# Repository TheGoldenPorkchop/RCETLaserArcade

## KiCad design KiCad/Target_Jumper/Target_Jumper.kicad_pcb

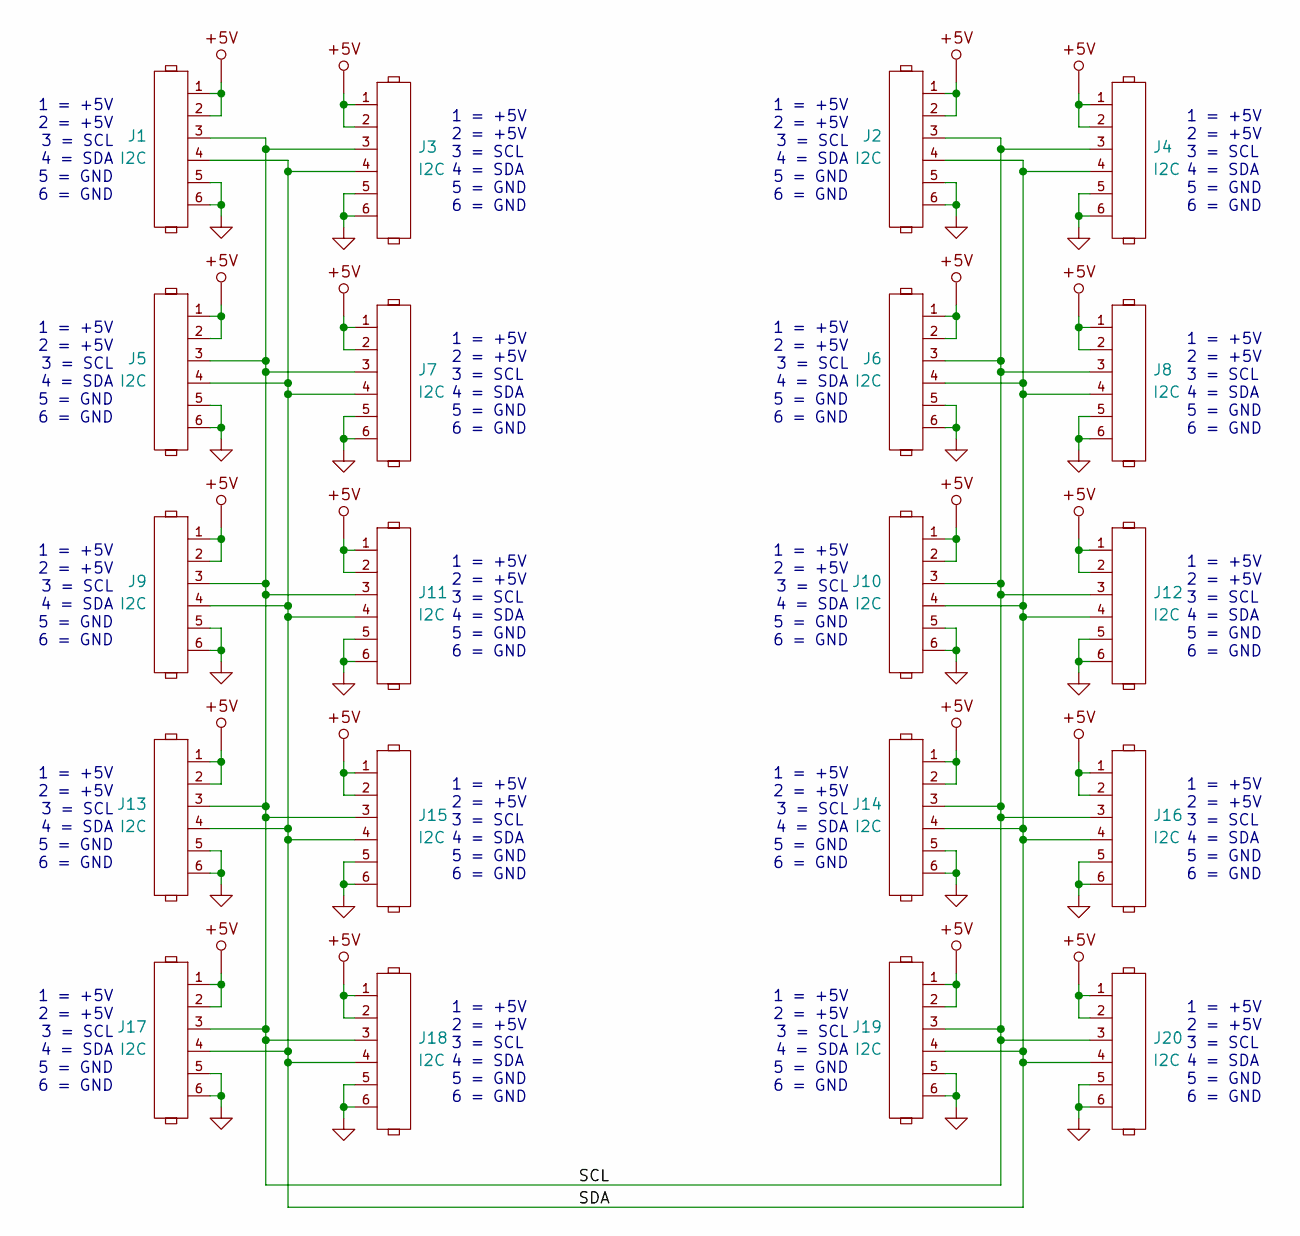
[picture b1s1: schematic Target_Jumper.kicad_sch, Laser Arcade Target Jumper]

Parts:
J1, J2, J3, J4, J5, J6, J7, J8, J9, J10, J11, J12, J13, J14, J15, J16, J17, J18, J19, J20: I2C; 1x6_100mil_Header

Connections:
+5V: J1.1, J1.2, J2.1, J2.2, J3.1, J3.2, J4.1, J4.2, J5.1, J5.2, J6.1, J6.2, J7.1, J7.2, J8.1, J8.2, J9.1, J9.2, J10.1, J10.2, J11.1, J11.2, J12.1, J12.2, J13.1, J13.2, J14.1, J14.2, J15.1, J15.2, J16.1, J16.2, J17.1, J17.2, J18.1, J18.2, J19.1, J19.2, J20.1, J20.2
/SCL: J1.3, J2.3, J3.3, J4.3, J5.3, J6.3, J7.3, J8.3, J9.3, J10.3, J11.3, J12.3, J13.3, J14.3, J15.3, J16.3, J17.3, J18.3, J19.3, J20.3
/SDA: J1.4, J2.4, J3.4, J4.4, J5.4, J6.4, J7.4, J8.4, J9.4, J10.4, J11.4, J12.4, J13.4, J14.4, J15.4, J16.4, J17.4, J18.4, J19.4, J20.4
GND: J1.5, J1.6, J2.5, J2.6, J3.5, J3.6, J4.5, J4.6, J5.5, J5.6, J6.5, J6.6, J7.5, J7.6, J8.5, J8.6, J9.5, J9.6, J10.5, J10.6, J11.5, J11.6, J12.5, J12.6, J13.5, J13.6, J14.5, J14.6, J15.5, J15.6, J16.5, J16.6, J17.5, J17.6, J18.5, J18.6, J19.5, J19.6, J20.5, J20.6

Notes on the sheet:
1 = +5V 2 = +5V 3 = SCL 4 = SDA 5 = GND 6 = GND

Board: 2 copper layers, 20 parts (0 on the bottom side), 4 nets, no tracks yet.

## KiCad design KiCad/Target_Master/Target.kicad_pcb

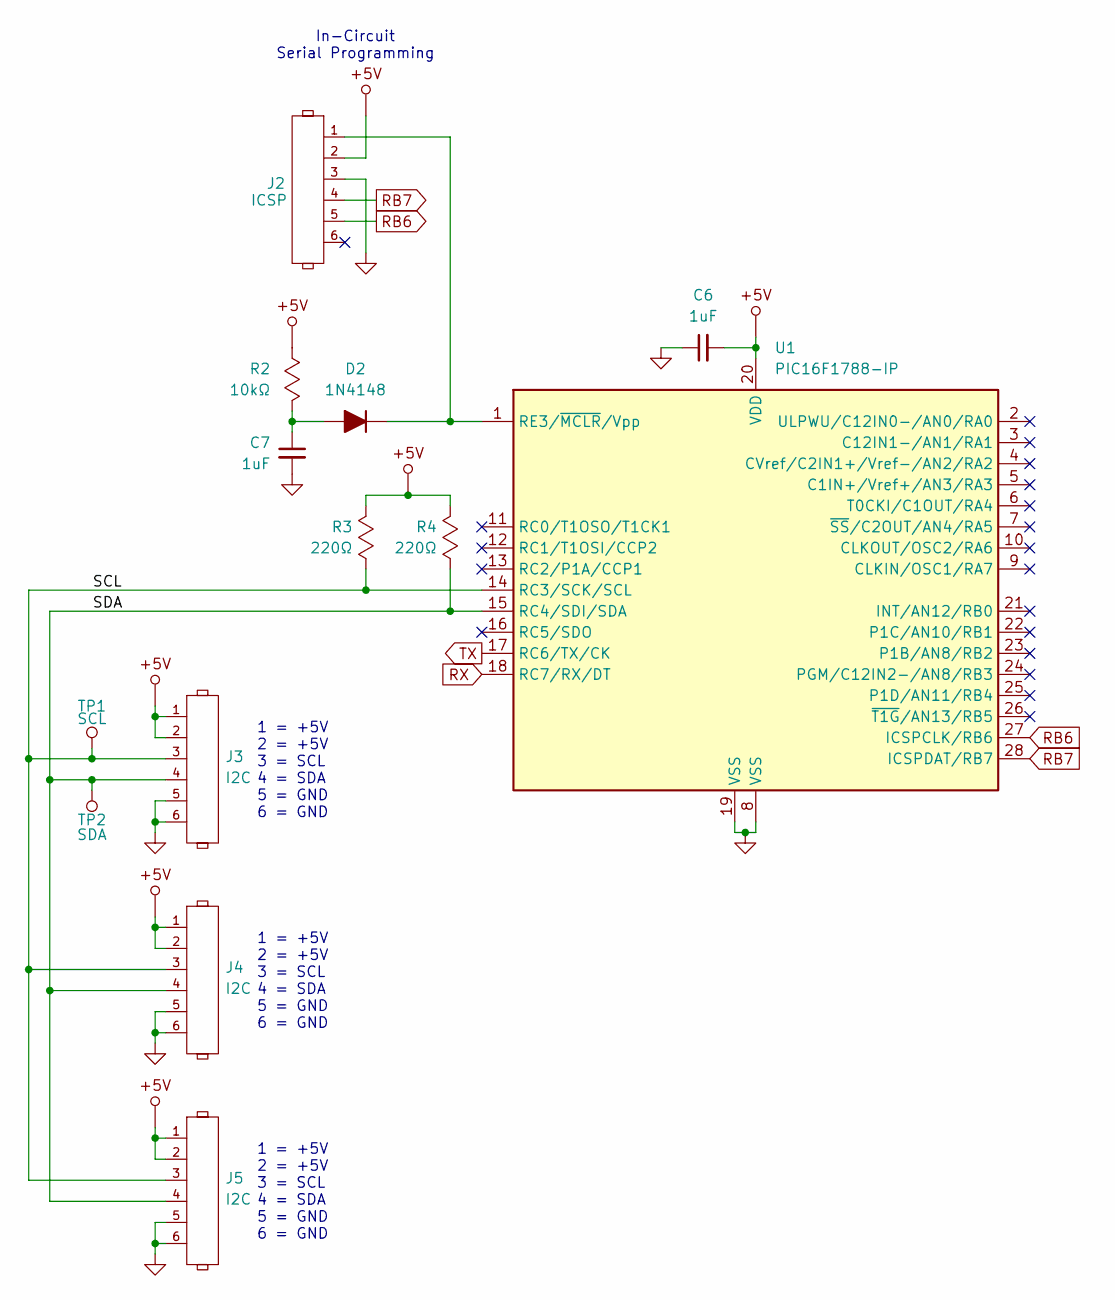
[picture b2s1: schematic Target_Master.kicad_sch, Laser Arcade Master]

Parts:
C6, C7: 1uF; C_0805_2012Metric_Pad1.18x1.45mm_HandSolder
D2: 1N4148; D_0805_2012Metric_Pad1.15x1.40mm_HandSolder
J2: ICSP; 1x6_100mil_Header
J3, J4, J5: I2C; 1x6_100mil_Header
R2: 10kΩ; R_0805_2012Metric_Pad1.20x1.40mm_HandSolder
R3, R4: 220Ω; R_0805_2012Metric_Pad1.20x1.40mm_HandSolder
TP1: SCL; 1x1_100mil_Header
TP2: SDA; 1x1_100mil_Header
U1: PIC16F1788-IP; SSOP-28

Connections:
+5V: C6.2, J2.2, J3.1, J3.2, J4.1, J4.2, J5.1, J5.2, R2.2, R3.1, R4.1, U1.20 (VDD); also elsewhere on the board
/Master/SCL: J3.3, J4.3, J5.3, R3.2, TP1.1, U1.14 (RC3/SCK/SCL)
/Master/SDA: J3.4, J4.4, J5.4, R4.2, TP2.1, U1.15 (RC4/SDI/SDA)
GND: C6.1, C7.2, J2.3, J3.5, J3.6, J4.5, J4.6, J5.5, J5.6, U1.8 (VSS), U1.19 (VSS); also elsewhere on the board
unnamed: C7.1, D2.2 (A), R2.1
unnamed: D2.1 (K), J2.1, U1.1 (RE3/~MCLR/Vpp)
RB6: J2.5, U1.27 (ICSPCLK/RB6)
RB7: J2.4, U1.28 (ICSPDAT/RB7)
RX: U1.18 (RC7/RX/DT); also elsewhere on the board
TX: U1.17 (RC6/TX/CK); also elsewhere on the board

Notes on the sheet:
In-Circuit Serial Programming
1 = +5V 2 = +5V 3 = SCL 4 = SDA 5 = GND 6 = GND

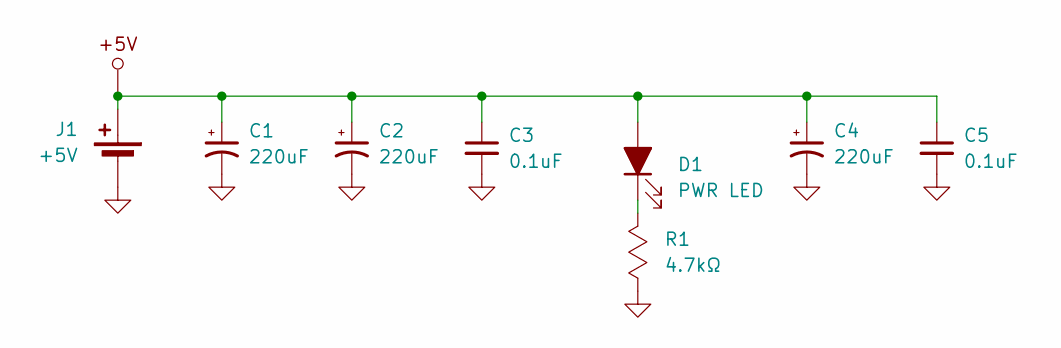
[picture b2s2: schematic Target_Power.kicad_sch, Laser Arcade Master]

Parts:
C1, C2, C4: 220uF; CP_Radial_D6.3mm_P2.50mm
C3, C5: 0.1uF; C_0805_2012Metric_Pad1.18x1.45mm_HandSolder
D1: PWR LED; LED_0805_2012Metric_Pad1.15x1.40mm_HandSolder
J1: +5V; AMASS_XT30PW-M_1x02_P2.50mm_Horizontal
R1: 4.7kΩ; R_0805_2012Metric_Pad1.20x1.40mm_HandSolder

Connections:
+5V: C1.1, C2.1, C3.1, C4.1, C5.1, D1.2 (A), J1.1 (+); also elsewhere on the board
GND: C1.2, C2.2, C3.2, C4.2, C5.2, J1.2 (-), R1.1; also elsewhere on the board
unnamed: D1.1 (K), R1.2

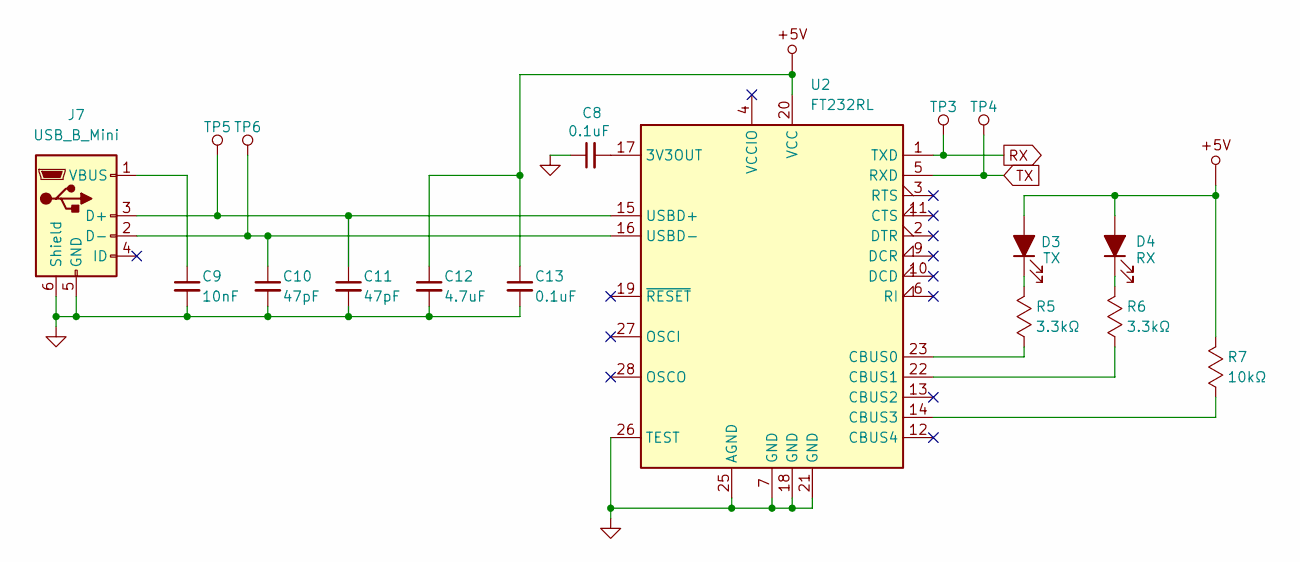
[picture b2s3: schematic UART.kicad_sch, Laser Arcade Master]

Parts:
C8, C13: 0.1uF; C_0805_2012Metric_Pad1.18x1.45mm_HandSolder
C9: 10nF; C_0805_2012Metric_Pad1.18x1.45mm_HandSolder
C10, C11: 47pF; C_0805_2012Metric_Pad1.18x1.45mm_HandSolder
C12: 4.7uF; C_0805_2012Metric_Pad1.18x1.45mm_HandSolder
D3: TX; LED_0805_2012Metric_Pad1.15x1.40mm_HandSolder
D4: RX; LED_0805_2012Metric_Pad1.15x1.40mm_HandSolder
J7: USB_B_Mini; USB_Micro-B_Amphenol
R5, R6: 3.3kΩ; R_0805_2012Metric_Pad1.20x1.40mm_HandSolder
R7: 10kΩ; R_0805_2012Metric_Pad1.20x1.40mm_HandSolder
TP3, TP4, TP5, TP6: 1x1_100mil_Header
U2: FT232RL; SSOP-28

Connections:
+5V: C12.1, C13.1, D3.2 (A), D4.2 (A), R7.2, U2.20 (VCC); also elsewhere on the board
GND: C8.1, C9.2, C10.2, C11.2, C12.2, C13.2, J7.5 (GND), J7.6 (Shield), U2.7 (GND), U2.18 (GND), U2.21 (GND), U2.25 (AGND), U2.26 (TEST); also elsewhere on the board
unnamed: D3.1 (K), R5.2
unnamed: D4.1 (K), R6.2
unnamed: C11.1, J7.3 (D+), TP5.1, U2.15 (USBD+)
unnamed: C10.1, J7.2 (D-), TP6.1, U2.16 (USBD-)
unnamed: C9.1, J7.1 (VBUS)
unnamed: C8.2, U2.17 (3V3OUT)
unnamed: R5.1, U2.23 (CBUS0)
unnamed: R6.1, U2.22 (CBUS1)
unnamed: R7.1, U2.14 (CBUS3)
RX: TP3.1, U2.1 (TXD); also elsewhere on the board
TX: TP4.1, U2.5 (RXD); also elsewhere on the board

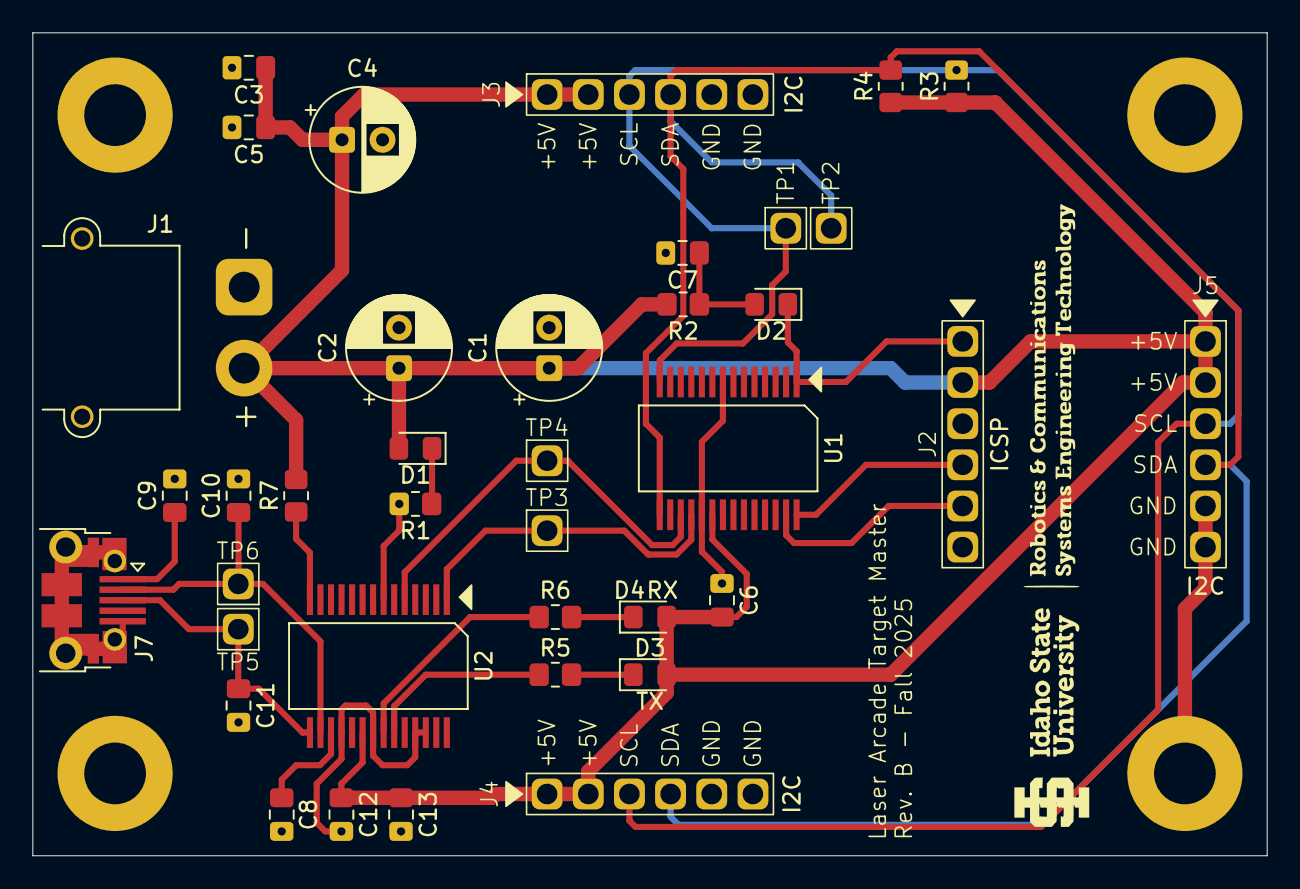
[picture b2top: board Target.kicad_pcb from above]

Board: 2 copper layers, 76.2 x 50.8 mm, 38 parts (0 on the bottom side), 20 nets.

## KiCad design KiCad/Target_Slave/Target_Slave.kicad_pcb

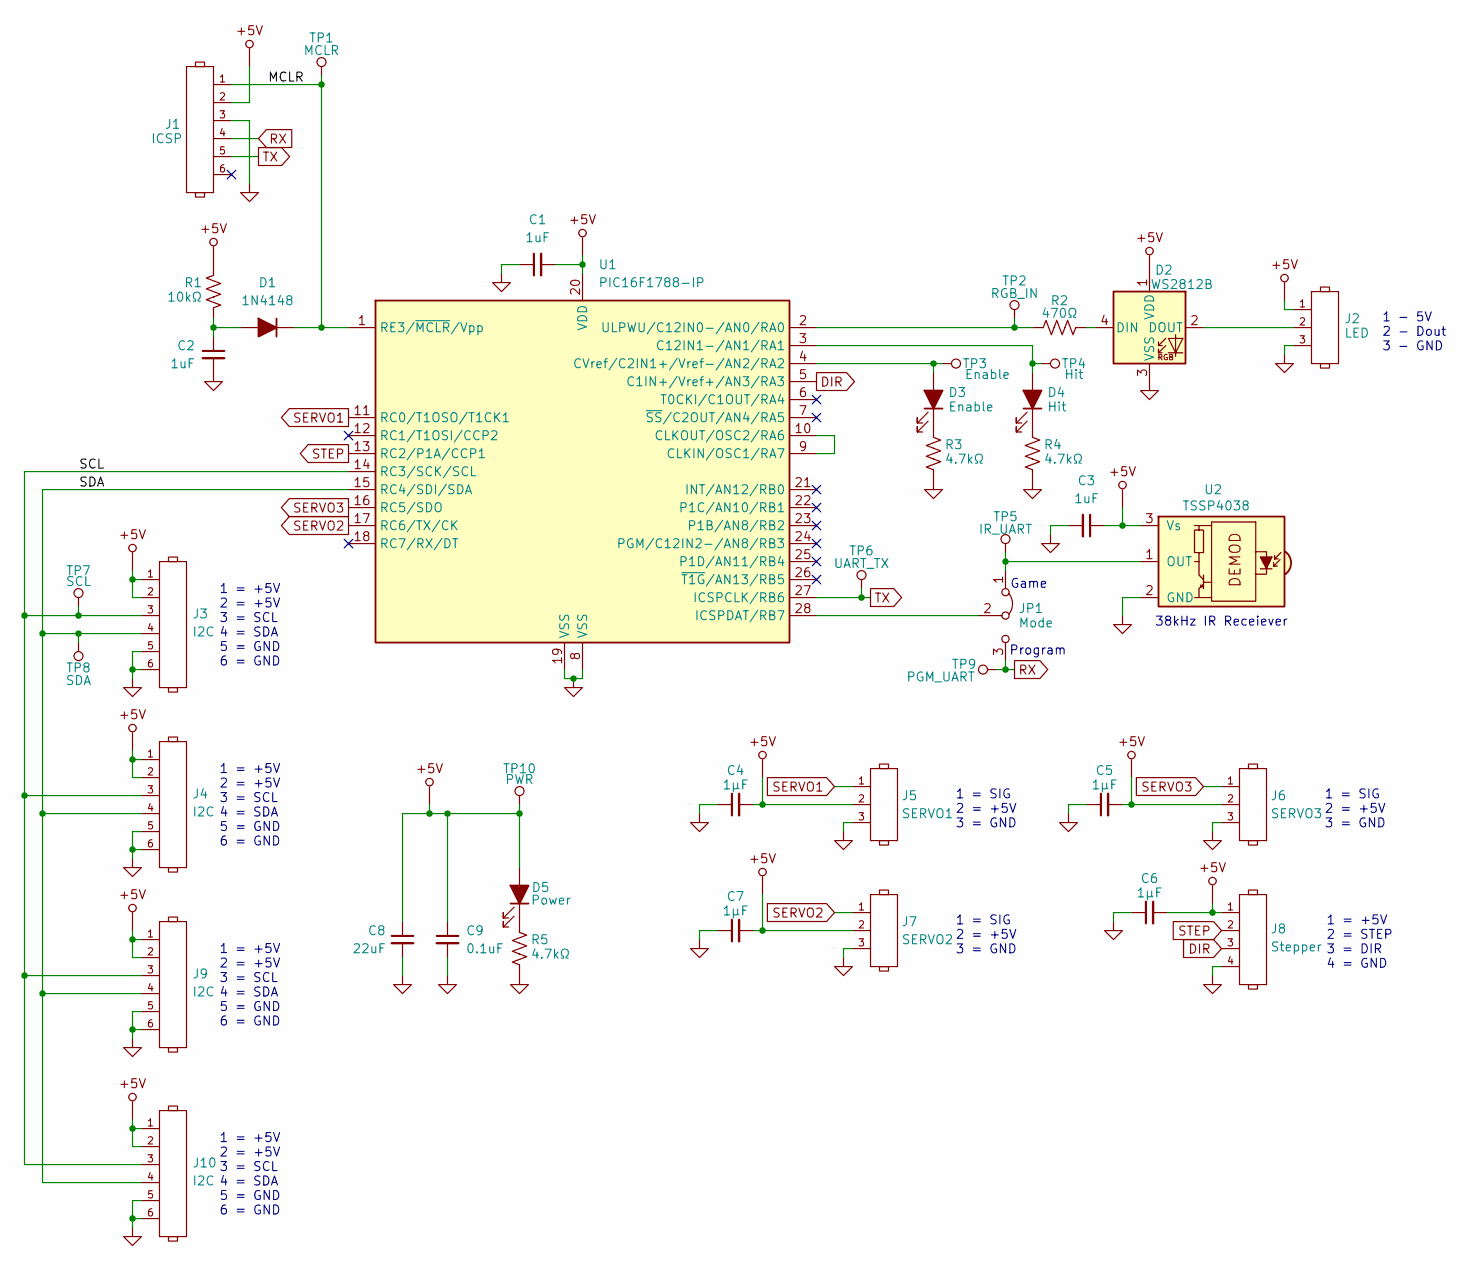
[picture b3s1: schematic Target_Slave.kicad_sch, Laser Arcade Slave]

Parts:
C1, C2, C3: 1uF; C_0805_2012Metric_Pad1.18x1.45mm_HandSolder
C4, C5, C6, C7: 1µF; C_0805_2012Metric_Pad1.18x1.45mm_HandSolder
C8: 22uF; C_0805_2012Metric_Pad1.18x1.45mm_HandSolder
C9: 0.1uF; C_0805_2012Metric_Pad1.18x1.45mm_HandSolder
D1: 1N4148; D_0805_2012Metric_Pad1.15x1.40mm_HandSolder
D2: WS2812B; LED_WS2812B_PLCC4_5.0x5.0mm_P3.2mm
D3: Enable; LED_0805_2012Metric_Pad1.15x1.40mm_HandSolder
D4: Hit; LED_0805_2012Metric_Pad1.15x1.40mm_HandSolder
D5: Power; LED_0805_2012Metric_Pad1.15x1.40mm_HandSolder
J1: ICSP; 1x6_100mil_Header
J2: LED; 1x3_100mil_Header_Locking
J3, J4, J9, J10: I2C; 1x6_100mil_Header
J5: SERVO1; 1x3_100mil_Header
J6: SERVO3; 1x3_100mil_Header
J7: SERVO2; 1x3_100mil_Header
J8: Stepper; 1x4_100mil_Header
JP1: Mode; 1x3_100mil_Header
R1: 10kΩ; R_0805_2012Metric_Pad1.20x1.40mm_HandSolder
R2: 470Ω; R_0805_2012Metric_Pad1.20x1.40mm_HandSolder
R3, R4, R5: 4.7kΩ; R_0805_2012Metric_Pad1.20x1.40mm_HandSolder
TP1: MCLR; 1x1_100mil_Header
TP2: RGB_IN; 1x1_100mil_Header
TP3: Enable; 1x1_100mil_Header
TP4: Hit; 1x1_100mil_Header
TP5: IR_UART; 1x1_100mil_Header
TP6: UART_TX; 1x1_100mil_Header
TP7: SCL; 1x1_100mil_Header
TP8: SDA; 1x1_100mil_Header
TP9: PGM_UART; 1x1_100mil_Header
TP10: PWR; 1x1_100mil_Header
U1: PIC16F1788-IP; SSOP-28
U2: TSSP4038; IR Receiver

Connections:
+5V: C1.2, C3.1, C4.2, C5.2, C6.2, C7.2, C8.1, C9.1, D2.1 (VDD), D5.2 (A), J1.2, J2.1, J3.1, J3.2, J4.1, J4.2, J5.2, J6.2, J7.2, J8.1, J9.1, J9.2, J10.1, J10.2, R1.1, TP10.1, U1.20 (VDD), U2.3 (Vs)
/MCLR: D1.1 (K), J1.1, TP1.1, U1.1 (RE3/~MCLR/Vpp)
/SCL: J3.3, J4.3, J9.3, J10.3, TP7.1, U1.14 (RC3/SCK/SCL)
/SDA: J3.4, J4.4, J9.4, J10.4, TP8.1, U1.15 (RC4/SDI/SDA)
DIR: J8.3, U1.5 (C1IN+/Vref+/AN3/RA3)
GND: C1.1, C2.2, C3.2, C4.1, C5.1, C6.1, C7.1, C8.2, C9.2, D2.3 (VSS), J1.3, J2.3, J3.5, J3.6, J4.5, J4.6, J5.3, J6.3, J7.3, J8.4, J9.5, J9.6, J10.5, J10.6, R3.2, R4.2, R5.2, U1.8 (VSS), U1.19 (VSS), U2.2 (GND)
unnamed: C2.1, D1.2 (A), R1.2
unnamed: D2.4 (DIN), R2.2
unnamed: D2.2 (DOUT), J2.2
unnamed: D3.2 (A), TP3.1, U1.4 (CVref/C2IN1+/Vref-/AN2/RA2)
unnamed: D3.1 (K), R3.1
unnamed: D4.2 (A), TP4.1, U1.3 (C12IN1-/AN1/RA1)
unnamed: D4.1 (K), R4.1
unnamed: D5.1 (K), R5.1
unnamed: JP1.1 (A), TP5.1, U2.1 (OUT)
unnamed: JP1.2 (C), U1.28 (ICSPDAT/RB7)
unnamed: U1.9 (CLKIN/OSC1/RA7), U1.10 (CLKOUT/OSC2/RA6)
unnamed: R2.1, TP2.1, U1.2 (ULPWU/C12IN0-/AN0/RA0)
RX: J1.4, JP1.3 (B), TP9.1
SERVO1: J5.1, U1.11 (RC0/T1OSO/T1CK1)
SERVO2: J7.1, U1.17 (RC6/TX/CK)
SERVO3: J6.1, U1.16 (RC5/SDO)
STEP: J8.2, U1.13 (RC2/P1A/CCP1)
TX: J1.5, TP6.1, U1.27 (ICSPCLK/RB6)

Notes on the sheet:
1 = +5V 2 = STEP 3 = DIR 4 = GND
1 = +5V 2 = +5V 3 = SCL 4 = SDA 5 = GND 6 = GND
Program
1 = SIG 2 = +5V 3 = GND
1 - 5V 2 - Dout 3 - GND
Game
38kHz IR Receiever

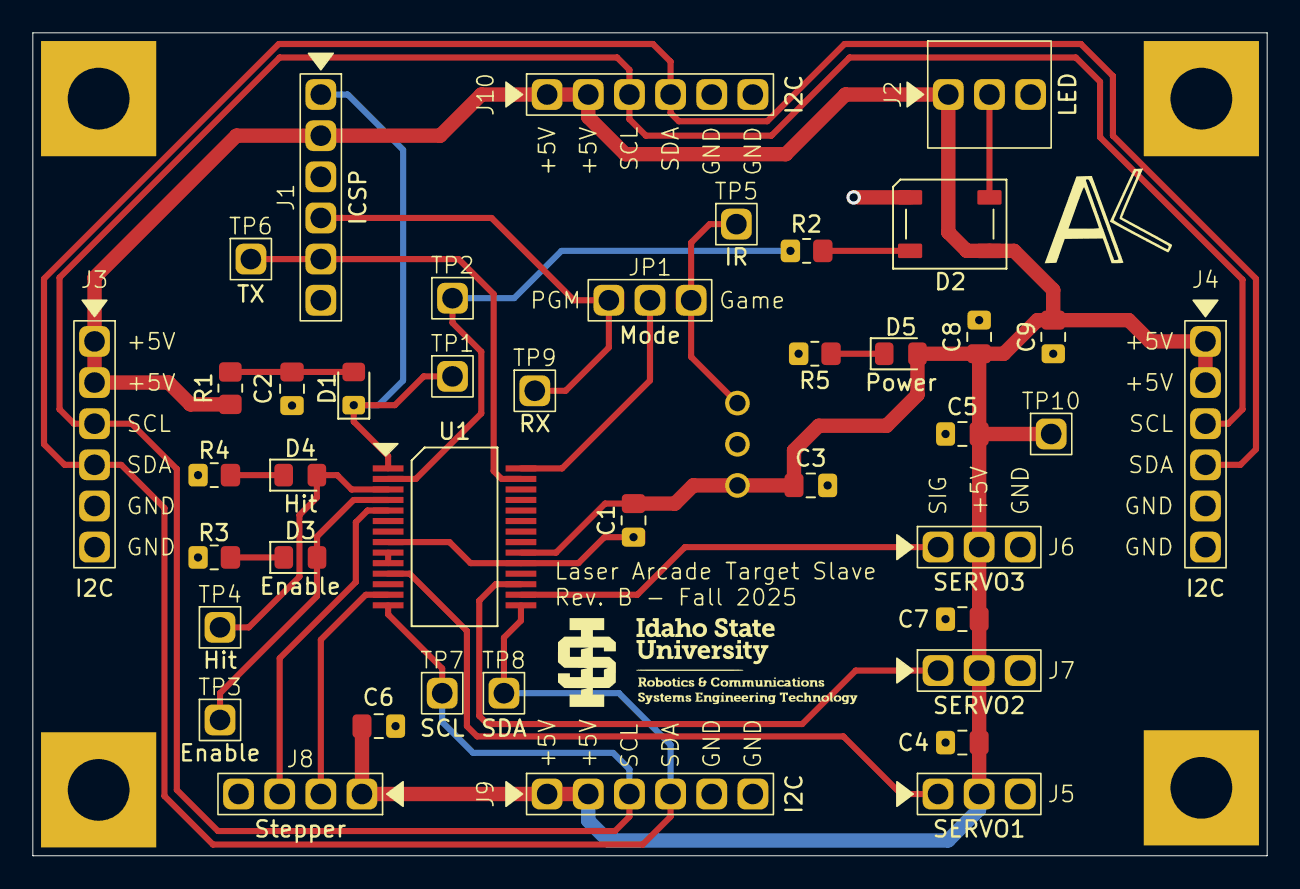
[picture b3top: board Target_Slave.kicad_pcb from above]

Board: 2 copper layers, 76.2 x 50.8 mm, 42 parts (1 on the bottom side), 24 nets.

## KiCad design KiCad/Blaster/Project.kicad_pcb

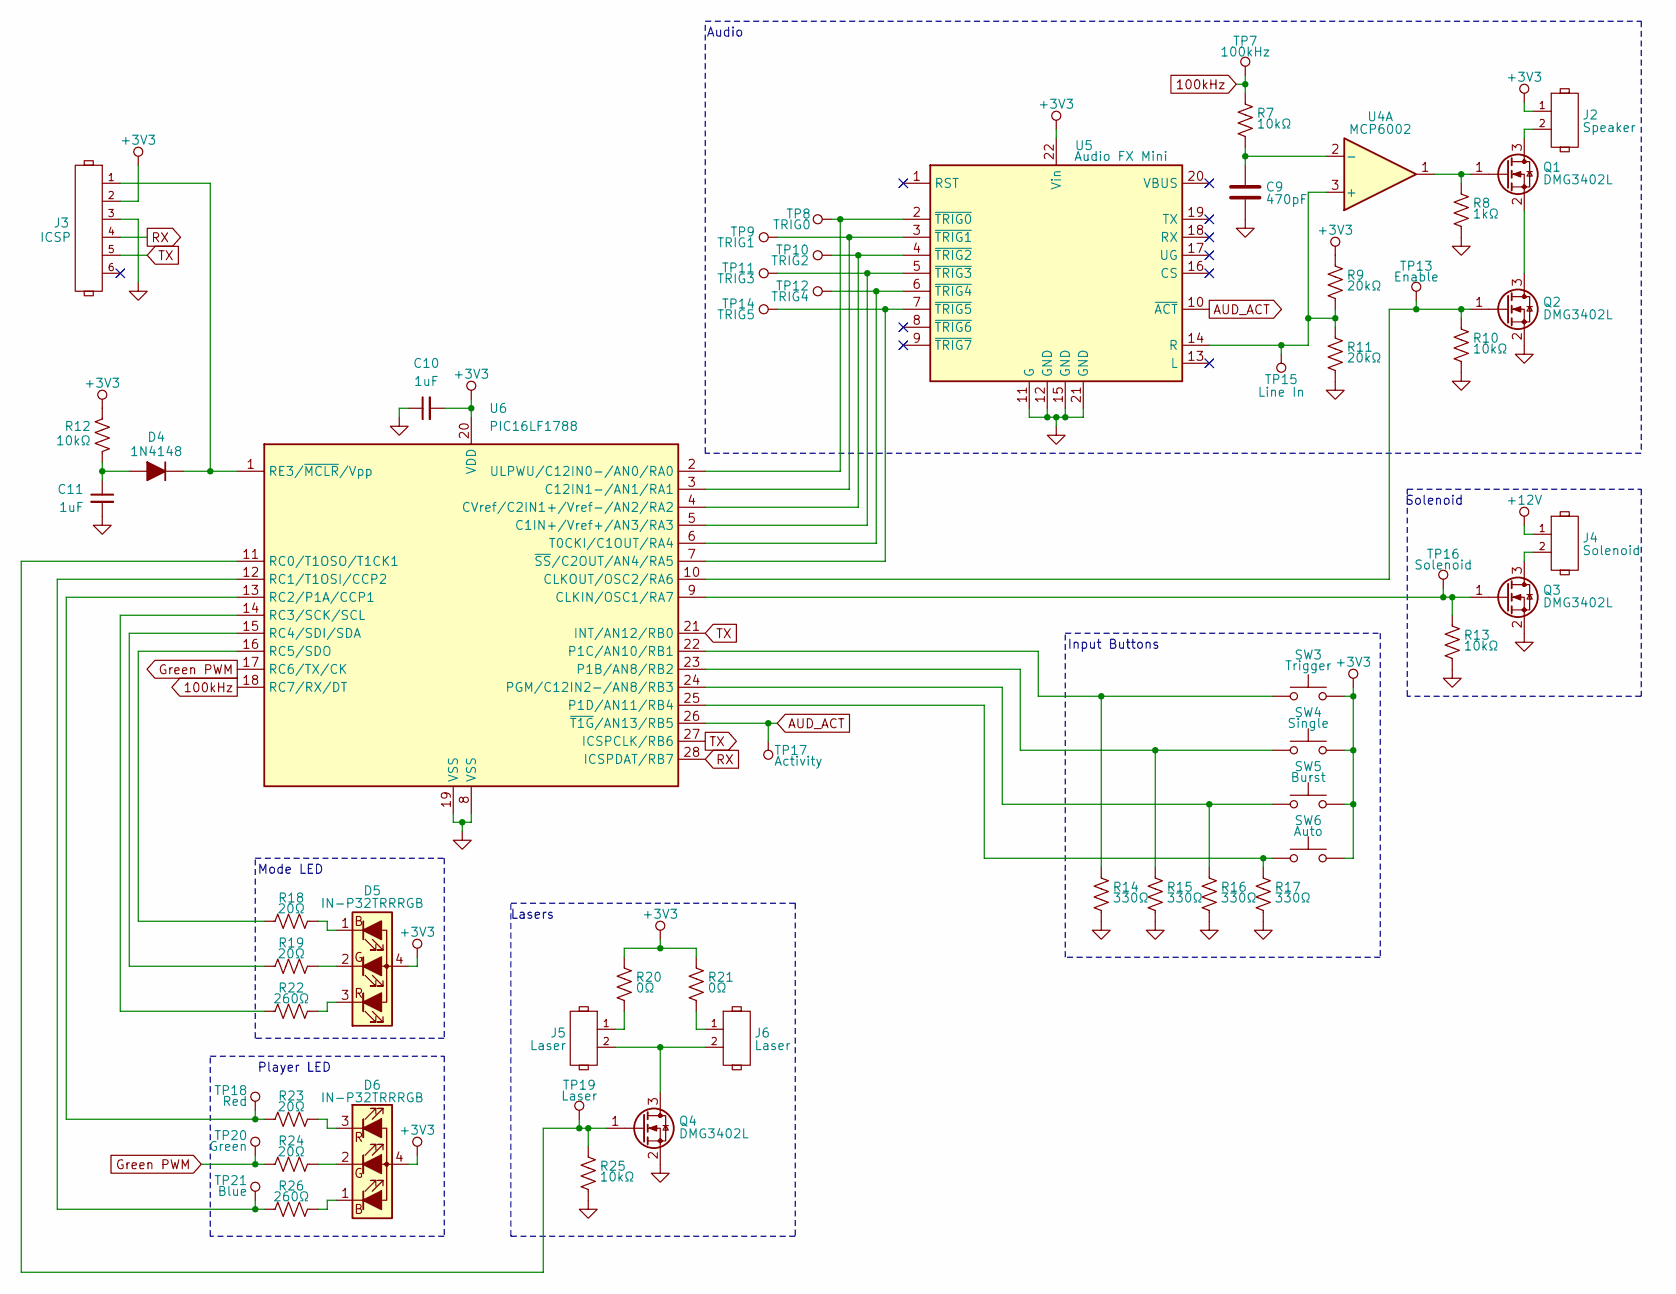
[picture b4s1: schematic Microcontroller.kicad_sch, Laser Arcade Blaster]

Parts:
C9: 470pF; C_0805_2012Metric_Pad1.18x1.45mm_HandSolder
C10, C11: 1uF; C_0805_2012Metric_Pad1.18x1.45mm_HandSolder
D4: 1N4148; D_0805_2012Metric_Pad1.15x1.40mm_HandSolder
D5, D6: IN-P32TRRRGB
J2: Speaker; 1x2_100mil_Header_Locking
J3: ICSP; 1x6_100mil_Header
J4: Solenoid; 1x2_100mil_Header_Locking
J5, J6: Laser; 1x2_100mil_Header_Locking
Q1, Q2, Q3, Q4: DMG3402L; SOT-23
R7, R10, R12, R13, R25: 10kΩ; R_0805_2012Metric_Pad1.20x1.40mm_HandSolder
R8: 1kΩ; R_0805_2012Metric_Pad1.20x1.40mm_HandSolder
R9, R11: 20kΩ; R_0805_2012Metric_Pad1.20x1.40mm_HandSolder
R14, R15, R16, R17: 330Ω; R_0805_2012Metric_Pad1.20x1.40mm_HandSolder
R18, R19, R23, R24: 20Ω; R_0805_2012Metric_Pad1.20x1.40mm_HandSolder
R20, R21: 0Ω; R_0805_2012Metric_Pad1.20x1.40mm_HandSolder
R22, R26: 260Ω; R_0805_2012Metric_Pad1.20x1.40mm_HandSolder
SW3: Trigger; SW_Tactile_SPST_Angled_PTS645Vx31-2LFS
SW4: Single; SW_PUSH_6mm_H5mm
SW5: Burst; SW_PUSH_6mm_H5mm
SW6: Auto; SW_PUSH_6mm_H5mm
TP7: 100kHz; 1x1_100mil_Header
TP8: TRIG0; 1x1_100mil_Header
TP9: TRIG1; 1x1_100mil_Header
TP10: TRIG2; 1x1_100mil_Header
TP11: TRIG3; 1x1_100mil_Header
TP12: TRIG4; 1x1_100mil_Header
TP13: Enable; 1x1_100mil_Header
TP14: TRIG5; 1x1_100mil_Header
TP15: Line In; 1x1_100mil_Header
TP16: Solenoid; 1x1_100mil_Header
TP17: Activity; 1x1_100mil_Header
TP18: Red; 1x1_100mil_Header
TP19: Laser; 1x1_100mil_Header
TP20: Green; 1x1_100mil_Header
TP21: Blue; 1x1_100mil_Header
U4: MCP6002; SOIC-8_3.9x4.9mm_P1.27mm
U5: Audio FX Mini; Adafruit_AudioFXMini
U6: PIC16LF1788; SSOP-28

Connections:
100kHz: R7.1, TP7.1, U6.18 (RC7/RX/DT)
+3V3: C10.2, D5.4 (A), D6.4 (A), J2.1, J3.2, R9.1, R12.1, R20.1, R21.1, SW3.2, SW4.2, SW5.2, SW6.2, U5.22 (Vin), U6.20 (VDD); also elsewhere on the board
+12V: J4.1; also elsewhere on the board
AUD_ACT: TP17.1, U5.10 (~ACT), U6.26 (~T1G/AN13/RB5)
GND: C9.2, C10.1, C11.2, J3.3, Q2.2 (S), Q3.2 (S), Q4.2 (S), R8.2, R10.2, R11.2, R13.2, R14.2, R15.2, R16.2, R17.2, R25.2, U5.11 (G), U5.12 (GND), U5.15 (GND), U5.21 (GND), U6.8 (VSS), U6.19 (VSS); also elsewhere on the board
Green PWM: R24.1, TP20.1, U6.17 (RC6/TX/CK)
unnamed: C11.1, D4.2 (A), R12.2
unnamed: D4.1 (K), J3.1, U6.1 (RE3/~MCLR/Vpp)
unnamed: D5.1 (BK), R18.2
unnamed: D5.2 (GK), R19.2
unnamed: D5.3 (RK), R22.2
unnamed: D6.1 (BK), R26.2
unnamed: D6.2 (GK), R24.2
unnamed: D6.3 (RK), R23.2
unnamed: J5.1, R20.2
unnamed: J6.1, R21.2
unnamed: J2.2, Q1.3 (D)
unnamed: Q1.1 (G), R8.1, U4.1
unnamed: Q1.2 (S), Q2.3 (D)
unnamed: Q2.1 (G), R10.1, TP13.1, U6.10 (CLKOUT/OSC2/RA6)
unnamed: J4.2, Q3.3 (D)
unnamed: Q3.1 (G), R13.1, TP16.1, U6.9 (CLKIN/OSC1/RA7)
unnamed: J5.2, J6.2, Q4.3 (D)
unnamed: Q4.1 (G), R25.1, TP19.1, U6.11 (RC0/T1OSO/T1CK1)
unnamed: R9.2, R11.1, TP15.1, U4.3 (+), U5.14 (R)
unnamed: C9.1, R7.2, U4.2 (-)
unnamed: TP8.1, U5.2 (~TRIG0), U6.2 (ULPWU/C12IN0-/AN0/RA0)
unnamed: TP9.1, U5.3 (~TRIG1), U6.3 (C12IN1-/AN1/RA1)
unnamed: TP10.1, U5.4 (~TRIG2), U6.4 (CVref/C2IN1+/Vref-/AN2/RA2)
unnamed: TP11.1, U5.5 (~TRIG3), U6.5 (C1IN+/Vref+/AN3/RA3)
unnamed: TP12.1, U5.6 (~TRIG4), U6.6 (T0CKI/C1OUT/RA4)
unnamed: TP14.1, U5.7 (~TRIG5), U6.7 (~SS/C2OUT/AN4/RA5)
unnamed: R15.1, SW4.1, U6.23 (P1B/AN8/RB2)
unnamed: R14.1, SW3.1, U6.22 (P1C/AN10/RB1)
unnamed: R17.1, SW6.1, U6.25 (P1D/AN11/RB4)
unnamed: R16.1, SW5.1, U6.24 (PGM/C12IN2-/AN8/RB3)
unnamed: R26.1, TP21.1, U6.12 (RC1/T1OSI/CCP2)
unnamed: R23.1, TP18.1, U6.13 (RC2/P1A/CCP1)
unnamed: R22.1, U6.14 (RC3/SCK/SCL)
unnamed: R19.1, U6.15 (RC4/SDI/SDA)
unnamed: R18.1, U6.16 (RC5/SDO)
RX: J3.4, U6.28 (ICSPDAT/RB7); also elsewhere on the board
TX: J3.5, U6.21 (INT/AN12/RB0), U6.27 (ICSPCLK/RB6); also elsewhere on the board

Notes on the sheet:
Solenoid
Mode LED
Player LED
Lasers
Input Buttons
Audio

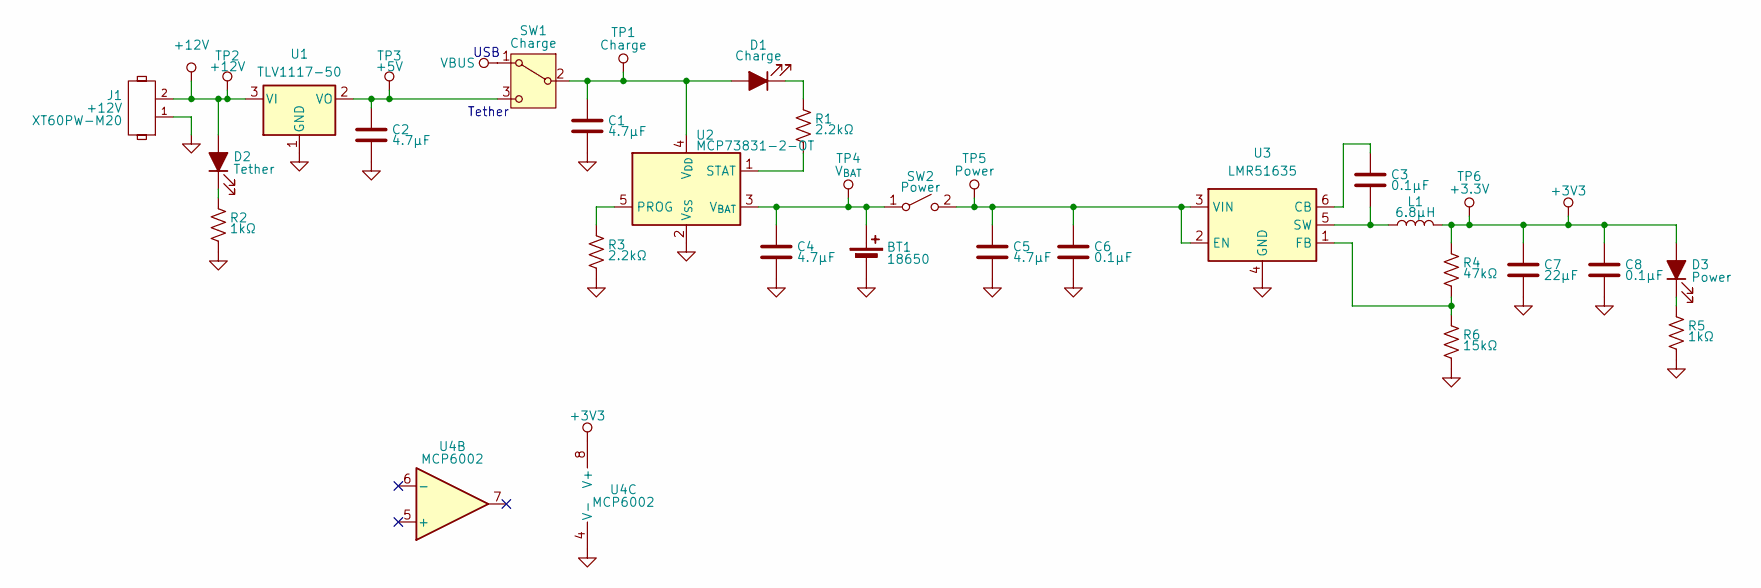
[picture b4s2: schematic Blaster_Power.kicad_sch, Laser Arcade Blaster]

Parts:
BT1: 18650; BatteryHolder_Keystone_1042_1x18650
C1, C2, C4, C5: 4.7µF; C_0805_2012Metric_Pad1.18x1.45mm_HandSolder
C3, C6, C8: 0.1µF; C_0805_2012Metric_Pad1.18x1.45mm_HandSolder
C7: 22µF; C_0805_2012Metric_Pad1.18x1.45mm_HandSolder
D1: Charge; LED_0805_2012Metric_Pad1.15x1.40mm_HandSolder
D2: Tether; LED_0805_2012Metric_Pad1.15x1.40mm_HandSolder
D3: Power; LED_0805_2012Metric_Pad1.15x1.40mm_HandSolder
J1: +12V; AMASS_XT60PW-M_1x02_P7.20mm_Horizontal
L1: 6.8µH; LA Blaster Power Inductor
R1, R3: 2.2kΩ; R_0805_2012Metric_Pad1.20x1.40mm_HandSolder
R2, R5: 1kΩ; R_0805_2012Metric_Pad1.20x1.40mm_HandSolder
R4: 47kΩ; R_0805_2012Metric_Pad1.20x1.40mm_HandSolder
R6: 15kΩ; R_0805_2012Metric_Pad1.20x1.40mm_HandSolder
SW1: Charge; T80-T
SW2: Power; LA Blaster Power Switch
TP1: Charge; 1x1_100mil_Header
TP2: +12V; 1x1_100mil_Header
TP3: +5V; 1x1_100mil_Header
TP4: V_{BAT}; 1x1_100mil_Header
TP5: Power; 1x1_100mil_Header
TP6: +3.3V; 1x1_100mil_Header
U1: TLV1117-50; SOT-223-3_TabPin2
U2: MCP73831-2-OT; SOT-23-5_HandSoldering
U3: LMR51635; SOT-23-6_Handsoldering
U4: MCP6002; SOIC-8_3.9x4.9mm_P1.27mm

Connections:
+3V3: C7.1, C8.1, D3.2 (A), L1.2, R4.1, TP6.1, U4.8 (V+); also elsewhere on the board
+12V: D2.2 (A), J1.2, TP2.1, U1.3 (VI); also elsewhere on the board
GND: BT1.2 (-), C1.2, C2.2, C4.2, C5.2, C6.2, C7.2, C8.2, J1.1, R2.2, R3.2, R5.2, R6.2, U1.1 (GND), U2.2 (V_{SS}), U3.4 (GND), U4.4 (V-); also elsewhere on the board
unnamed: BT1.1 (+), C4.1, SW2.1 (A), TP4.1, U2.3 (V_{BAT})
unnamed: C1.1, D1.2 (A), SW1.2 (B), TP1.1, U2.4 (V_{DD})
unnamed: D1.1 (K), R1.1
unnamed: D2.1 (K), R2.1
unnamed: D3.1 (K), R5.1
unnamed: C2.1, SW1.3 (C), TP3.1, U1.2 (VO)
unnamed: C5.1, C6.1, SW2.2 (B), TP5.1, U3.2 (EN), U3.3 (VIN)
unnamed: R3.1, U2.5 (PROG)
unnamed: R1.2, U2.1 (STAT)
unnamed: C3.1, U3.6 (CB)
unnamed: R4.2, R6.1, U3.1 (FB)
unnamed: C3.2, L1.1, U3.5 (SW)
VBUS: SW1.1 (A); also elsewhere on the board

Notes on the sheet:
Tether
USB

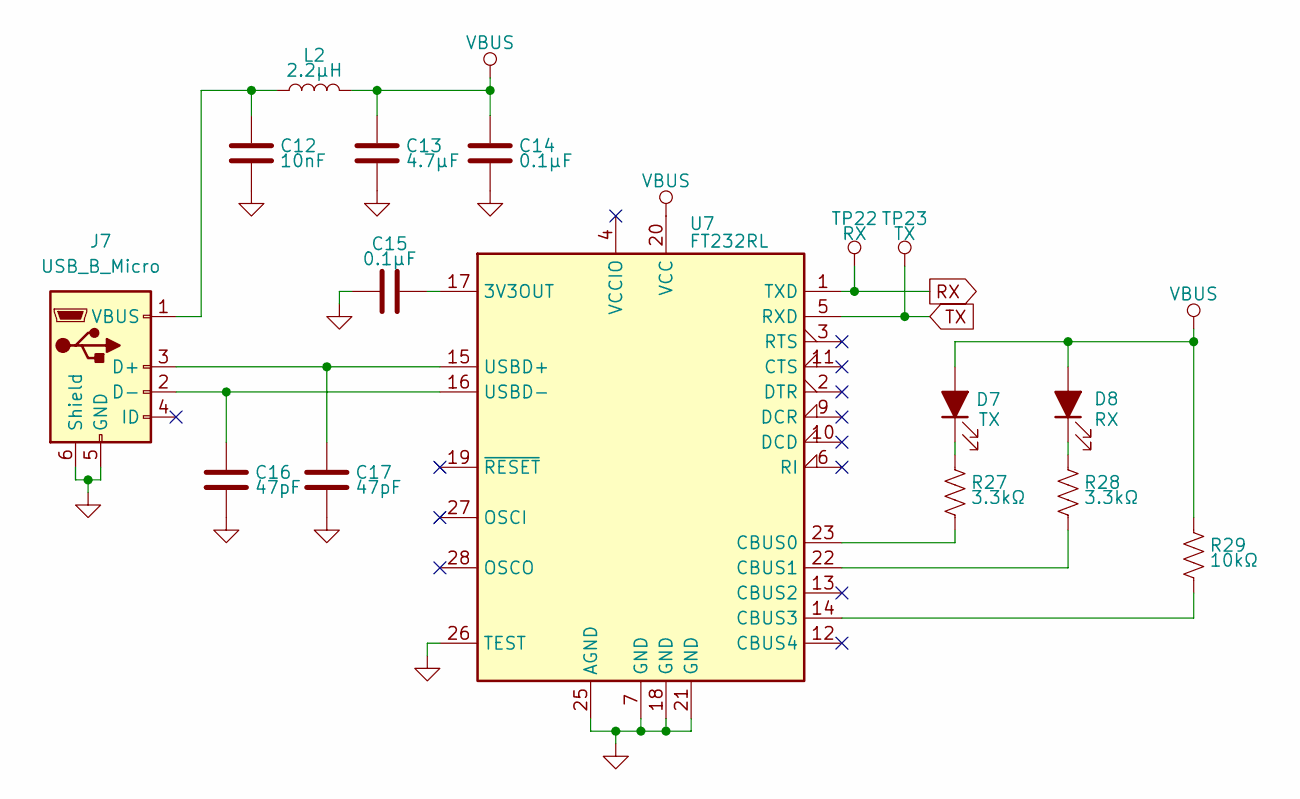
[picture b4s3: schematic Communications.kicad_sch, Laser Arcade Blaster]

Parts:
C12: 10nF; C_0805_2012Metric_Pad1.18x1.45mm_HandSolder
C13: 4.7µF; C_0805_2012Metric_Pad1.18x1.45mm_HandSolder
C14, C15: 0.1µF; C_0805_2012Metric_Pad1.18x1.45mm_HandSolder
C16, C17: 47pF; C_0805_2012Metric_Pad1.18x1.45mm_HandSolder
D7: TX; LED_0805_2012Metric_Pad1.15x1.40mm_HandSolder
D8: RX; LED_0805_2012Metric_Pad1.15x1.40mm_HandSolder
J7: USB_B_Micro; USB_Micro-B_Amphenol
L2: 2.2µH; L_0805_2012Metric_Pad1.15x1.40mm_HandSolder
R27, R28: 3.3kΩ; R_0805_2012Metric_Pad1.20x1.40mm_HandSolder
R29: 10kΩ; R_0805_2012Metric_Pad1.20x1.40mm_HandSolder
TP22: RX; 1x1_100mil_Header
TP23: TX; 1x1_100mil_Header
U7: FT232RL; SSOP-28

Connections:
GND: C12.2, C13.2, C14.2, C15.1, C16.2, C17.2, J7.5 (GND), J7.6 (Shield), U7.7 (GND), U7.18 (GND), U7.21 (GND), U7.25 (AGND), U7.26 (TEST); also elsewhere on the board
unnamed: D7.1 (K), R27.1
unnamed: D8.1 (K), R28.1
unnamed: C17.1, J7.3 (D+), U7.15 (USBD+)
unnamed: C16.1, J7.2 (D-), U7.16 (USBD-)
unnamed: C12.1, J7.1 (VBUS), L2.1
unnamed: C15.2, U7.17 (3V3OUT)
unnamed: R27.2, U7.23 (CBUS0)
unnamed: R28.2, U7.22 (CBUS1)
unnamed: R29.2, U7.14 (CBUS3)
RX: TP22.1, U7.1 (TXD); also elsewhere on the board
TX: TP23.1, U7.5 (RXD); also elsewhere on the board
VBUS: C13.1, C14.1, D7.2 (A), D8.2 (A), L2.2, R29.1, U7.20 (VCC); also elsewhere on the board
